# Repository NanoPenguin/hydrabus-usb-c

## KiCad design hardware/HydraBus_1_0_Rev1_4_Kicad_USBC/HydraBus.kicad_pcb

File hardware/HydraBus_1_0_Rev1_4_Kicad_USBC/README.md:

HydraBus Rev 1.4 with USB-C
========

This is a modified version of the Rev 1.4 with USB-C connectors instead of micro-USB.

The second connector had OTG-support. I could not see I would have much use for that so I forced the connector to act as a sink using the bridged jumper underneath the board. To make it possible to configure this though the jumper can be cut and pin headers soldered to enable sink/source selection. **These headers must not be used unless the jumper is cut or there will be a short.** There are ofcourse ICs to do this selection from the STM32 using the same pin previously used for USBID on the micro-connector but I did not find that necessary.

It is worth noting that in order to fit the components I had to move some stuff around. The routing in this modified version is much worse than that in the original. This is especially noteworthy for the differential USB communication lines which have not been tuned. So far everything seems to work fine though.

For licensing etc, please see the [original HydraBus repository](https://github.com/hydrabus/hydrabus).

Thank you to HydraBus for an amazing product.

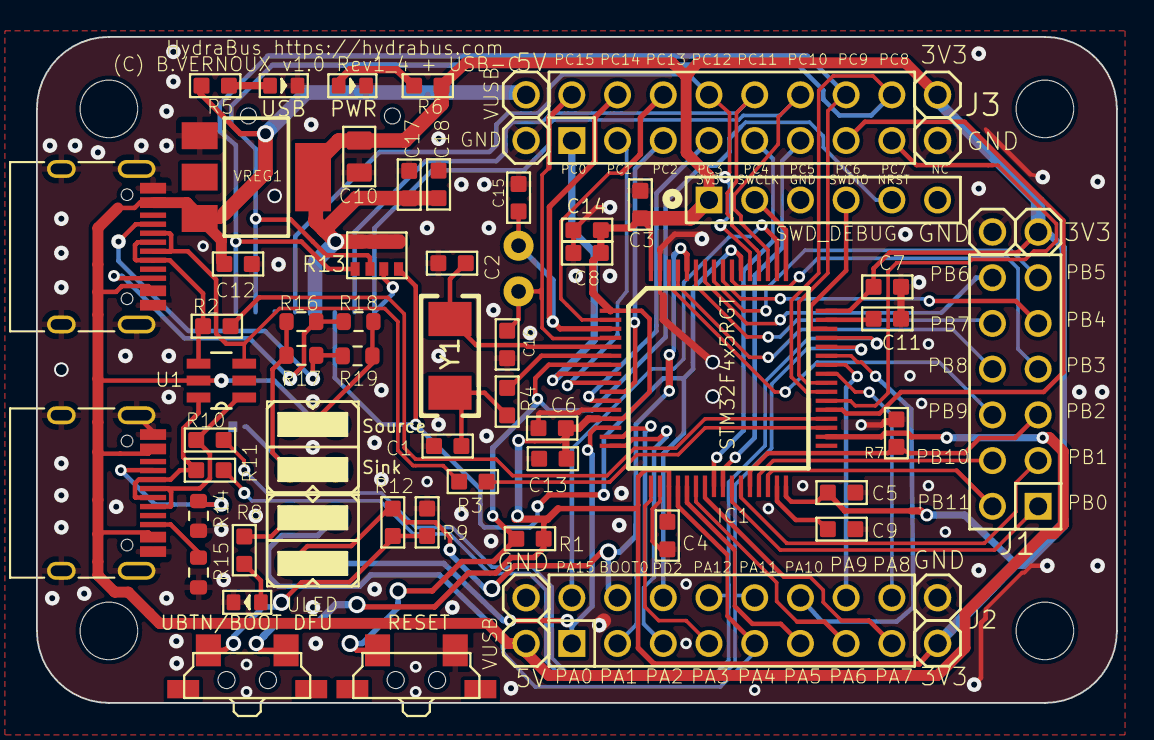
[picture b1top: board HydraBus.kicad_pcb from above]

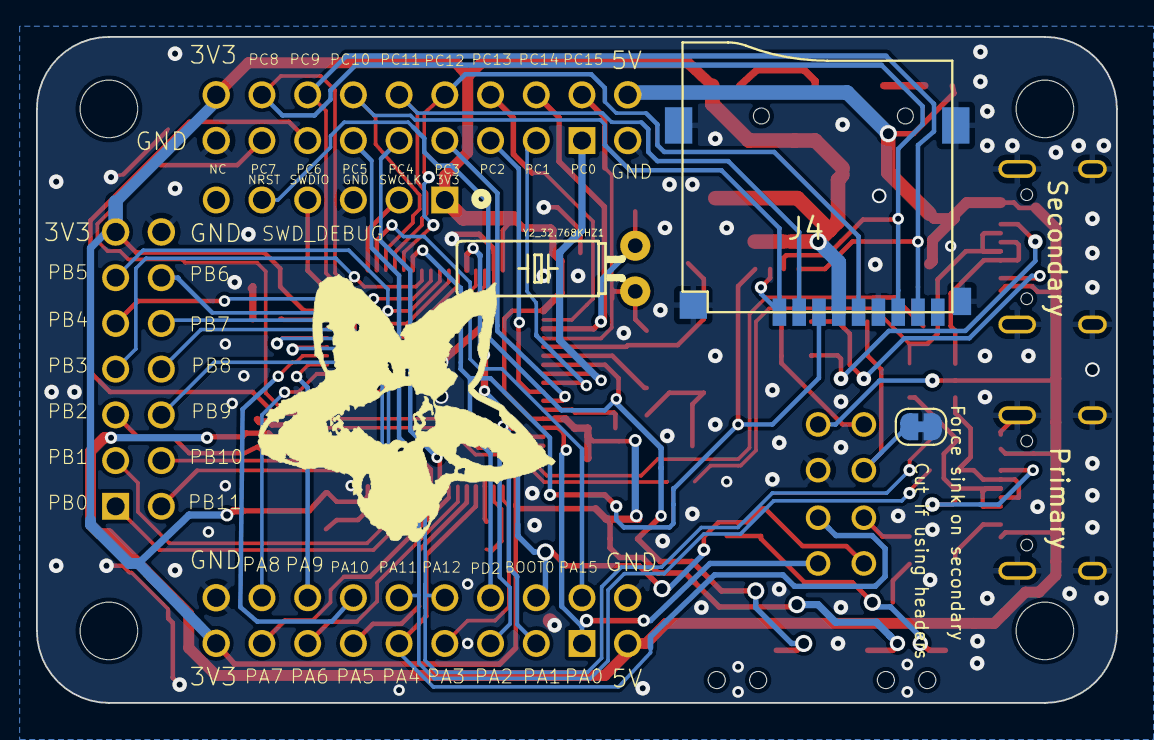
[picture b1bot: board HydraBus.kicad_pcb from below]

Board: 2 copper layers, 60.0 x 37.0 mm, 72 parts (3 on the bottom side), 72 nets.

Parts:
C1, C2: 18pF; C0603
C3, C4, C5, C6, C7, C8, C12, C18: 100nF; C0603
C9, C11, C13, C17: 2.2uF; C0603
C10: 10uF; C0805
C14: 4.7uF; C0603
C15, C16: 8pF; C0603
DP6037_V1: DP6037_V1
IC1: STM32F4x5RGT; LQFP64
J1: CON_HEADER_2X06; M2X6
J2, J3: CON_HEADER_2X08; M2X8
J4: MICRO-SDCARD-CONNECTOR-3300060P1; 9P-SMD-W-RING
J5: CON_HEADER_1X06-PTH; M1X6
J6, J7: USB_C_Receptacle_USB2.0; USB_C_Receptacle_HRO_TYPE-C-31-M-12
JMP1, JMP2: JP2QE; JP2Q
JMP_UBTN1, JMP_UBTN2: SHORT-JUMPER-2P-3460440P1; 2P-2.54
JMP_ULED1, JMP_ULED2: SHORT-JUMPER-2P-3460440P1; 2P-2.54
JP1, JP4: 5V; 1X01
JP2, JP3, JP6, JP8, JP10: GND; 1X01
JP5: SolderJumper_2_Bridged; SolderJumper-2_P1.3mm_Bridged_RoundedPad1.0x1.5mm
JP7, JP9, JP11: 3V3; 1X01
PWR1: LED; LED0603
R1, R7, R9, R12: 10K; R0603
R2, R3, R10, R11: 22; R0603
R4: 220; R0603
R5: 3.3K; R0603
R6, R8: 2.2K; R0603
R13: 10K; R1206-8
R14, R15, R16, R17: 5.1K; R_0603_1608Metric
R18, R19: 56K; R_0603_1608Metric
RESET1: BUTTON-2P-REINFORCE-3100060P1; 4P-SMD-7.0X3.5X3.5H-90D
U1: IP4220CZ6; SOT95P275X110-6N
UBTN1: BUTTON-2P-REINFORCE-3100060P1; 4P-SMD-7.0X3.5X3.5H-90D
ULED1: LED; LED0603
USB3: LED; LED0603
VREG1: LD1117AS33TR; SOT223
Y1: SMD-5032_2P_8MHz_20ppm_20pF; SMD-5032_2P
Y2_32.768KHZ1: 32.768KHz; TC38H

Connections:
+3V3: C3.1, C4.1, C5.2, C6.1, C7.1, C8.1, C10.1, C13.1, C14.1, C17.2, C18.1, IC1.1 (VBAT), IC1.13 (VDDA), IC1.19 (VDD@19), IC1.32 (VDD@32), IC1.48 (VDD@48), IC1.64 (VDD@64), J4.4 (VDD), J5.1, JP7.1, JP9.1, JP11.1, R1.2, R6.2, R13.5 (2), R13.6 (2), R13.7 (2), R13.8 (2), UBTN1.2, VREG1.4 (OUT)
/BOOT0: IC1.60 (BOOT0), J2.4, JMP1.4 (2), R12.2
/NRST: IC1.7 (NRST), J5.5, R1.1, RESET1.1
/PA0: IC1.14 (PA0), J2.1, JMP1.3 (1)
/PA1: IC1.15 (PA1), J2.3
/PA2: IC1.16 (PA2), J2.5
/PA3: IC1.17 (PA3), J2.7
/PA4: IC1.20 (PA4), J2.9, JMP1.1
/PA5: IC1.21 (PA5), J2.11
/PA6: IC1.22 (PA6), J2.13
/PA7: IC1.23 (PA7), J2.15
/PA8: IC1.41 (PA8), J2.16
/PA9: IC1.42 (PA9), J2.14
/PA10: IC1.43 (PA10), J2.12
/PA15: IC1.50 (PA15), J2.2
/PB0: IC1.26 (PB0), J1.1
/PB1: IC1.27 (PB1), J1.3
/PB2: IC1.28 (PB2), J1.5, R7.1
/PB3: IC1.55 (PB3), J1.7
/PB4: IC1.56 (PB4), J1.9
/PB5: IC1.57 (PB5), J1.11
/PB6: IC1.58 (PB6), J1.12
/PB7: IC1.59 (PB7), J1.10
/PB8: IC1.61 (PB8), J1.8
/PB9: IC1.62 (PB9), J1.6
/PB10: IC1.29 (PB10), J1.4
/PB11: IC1.30 (PB11), J1.2
/PC0: IC1.8 (PC0), J3.1
/PC1: IC1.9 (PC1), J3.3
/PC2: IC1.10 (PC2), J3.5
/PC3: IC1.11 (PC3), J3.7
/PC4: IC1.24 (PC4), J3.9
/PC5: IC1.25 (PC5), J3.11
/PC6: IC1.37 (PC6), J3.13
/PC7: IC1.38 (PC7), J3.15
/PC8: IC1.39 (PC8), J3.16, J4.7 (DO), R13.2 (1)
/PC9: IC1.40 (PC9), J3.14, J4.8 (DATA1), R13.1
/PC10: IC1.51 (PC10), J3.12, J4.1 (DATA2), R13.3 (1)
/PC11: IC1.52 (PC11), J3.10, J4.2 (CS)
/PC12: IC1.53 (PC12), J3.8, J4.5 (SCLK)
/PC13: IC1.2 (PC13), J3.6
/PC14: C15.1, IC1.3 (PC14), J3.4, Y2_32.768KHZ1.2
/PC15: C16.1, IC1.4 (PC15), J3.2, Y2_32.768KHZ1.1
/PD2: IC1.54 (PD2), J2.6, J4.3 (DI), R13.4 (1)
/PH0: C2.1, IC1.5 (PH0), Y1.1 (OSC1)
/PH1: IC1.6 (PH1), R4.2
/SWD_SWCLK: IC1.49 (PA14), J5.2
/SWD_SWDIO: IC1.46 (PA13), J5.4
/USB0D_N: IC1.44 (PA11), J2.10, R11.2
/USB0D_P: IC1.45 (PA12), J2.8, R10.2
/USB1D_N: IC1.35 (PB14), R3.2
/USB1D_P: IC1.36 (PB15), R2.2
/VCAP_1: C9.2, IC1.31 (VCAP_1)
/VCAP_2: C11.1, IC1.47 (VCAP_2)
GND: C1.2, C2.2, C3.2, C4.2, C5.1, C6.2, C7.2, C8.2, C9.1, C10.2, C11.2, C12.2, C13.2, C14.2, C15.2, C16.2, C17.1, C18.2, IC1.12 (VSSA), IC1.18 (VSS@18), IC1.63 (VSS@63), J4.6 (VSS), J4.G1, J4.G2, J4.G3, J4.G4, J5.3, J6.A1 (GND), J6.A12 (GND), J6.B1 (GND), J6.B12 (GND), J6.S1 (SHIELD), J7.A1 (GND), J7.A12 (GND), J7.B1 (GND), J7.B12 (GND), J7.S1 (SHIELD), JMP2.2, JP2.1, JP3.1, JP5.2 (B), JP6.1, JP8.1, JP10.1, PWR1.-, R7.2, R9.2, R14.2, R15.2, RESET1.2, U1.2 (GND), ULED1.-, USB3.-, VREG1.1 (ADJ)
unnamed: J6.A5 (CC1), R14.1
unnamed: J6.B5 (CC2), R15.1
unnamed: JMP1.2, R8.2
unnamed: JMP2.3 (1), R18.2, R19.2
unnamed: JMP2.1, JP5.1 (A), R16.2, R17.2
unnamed: PWR1.+, R6.1
unnamed: R5.2, USB3.+
unnamed: R8.1, ULED1.+
unnamed: R9.1, R12.1, UBTN1.1
unnamed: C1.1, R4.1, Y1.2 (OSC2)
SUPPLY_VUSB: C12.1, IC1.34 (PB13), J6.A4 (VBUS), J6.A9 (VBUS), J6.B4 (VBUS), J6.B9 (VBUS), J7.A4 (VBUS), J7.A9 (VBUS), J7.B4 (VBUS), J7.B9 (VBUS), JMP2.4 (2), JP1.1, JP4.1, R5.1, U1.5 (VP), VREG1.3 (IN)
USB0_D+: J6.A6 (D+), J6.B6 (D+), R10.1, U1.1 (I/O_4)
USB0_D-: J6.A7 (D-), J6.B7 (D-), R11.1, U1.6 (I/O_2)
USB1_CC1: J7.A5 (CC1), R17.1, R19.1
USB1_CC2: J7.B5 (CC2), R16.1, R18.1
USB1_D+: J7.A6 (D+), J7.B6 (D+), R2.1, U1.4 (I/O_3)
USB1_D-: J7.A7 (D-), J7.B7 (D-), R3.1, U1.3 (I/O)

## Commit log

2023-07-11 Added USB-C version
